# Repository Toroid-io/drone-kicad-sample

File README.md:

## drone-kicad sample board

This is a small board to demonstrate how to generate KiCad output files
with [drone](https://github.com/drone/drone).

Please check `.drone.yml`.

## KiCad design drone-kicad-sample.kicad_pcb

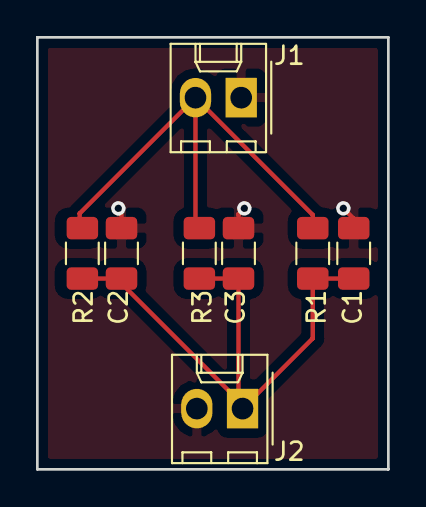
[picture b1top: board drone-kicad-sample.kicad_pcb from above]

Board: 2 copper layers, 19.5 x 24.0 mm, 8 parts (0 on the bottom side), 3 nets.

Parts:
C1: 1u; C_1206_3216Metric
C2: 0.1u; C_1206_3216Metric
C3: 10u; C_1206_3216Metric
J1, J2: Screw_Terminal_01x02; Molex_KK-254_AE-6410-02A_1x02_P2.54mm_Vertical
R1: 100k; R_1206_3216Metric
R2: 10k; R_1206_3216Metric
R3: 1M; R_1206_3216Metric

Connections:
GND: C1.2, C2.2, C3.2, J1.1, J2.2
unnamed: C1.1, C2.1, C3.1, J2.1, R1.1, R2.1, R3.1
unnamed: J1.2, R1.2, R2.2, R3.2

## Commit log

2018-10-09 Add sample PCB
2018-10-09 No spaces in variants please
2018-10-09 Deploy on push
2018-10-09 Move componentes
2018-10-10 Fix pipeline and board
2018-10-10 Add README with badge
2018-10-10 Add comments to pipeline [skip ci]
2018-11-05 Use v0.5.3 plugin
2018-11-05 Use v0.5.4 plugin
2018-11-26 Add BOM generation
2018-11-26 Only deploy if we push to the master branch
2018-12-04 Add cloud.drone.io badge
2018-12-05 Add drone 1.0 pipeline
